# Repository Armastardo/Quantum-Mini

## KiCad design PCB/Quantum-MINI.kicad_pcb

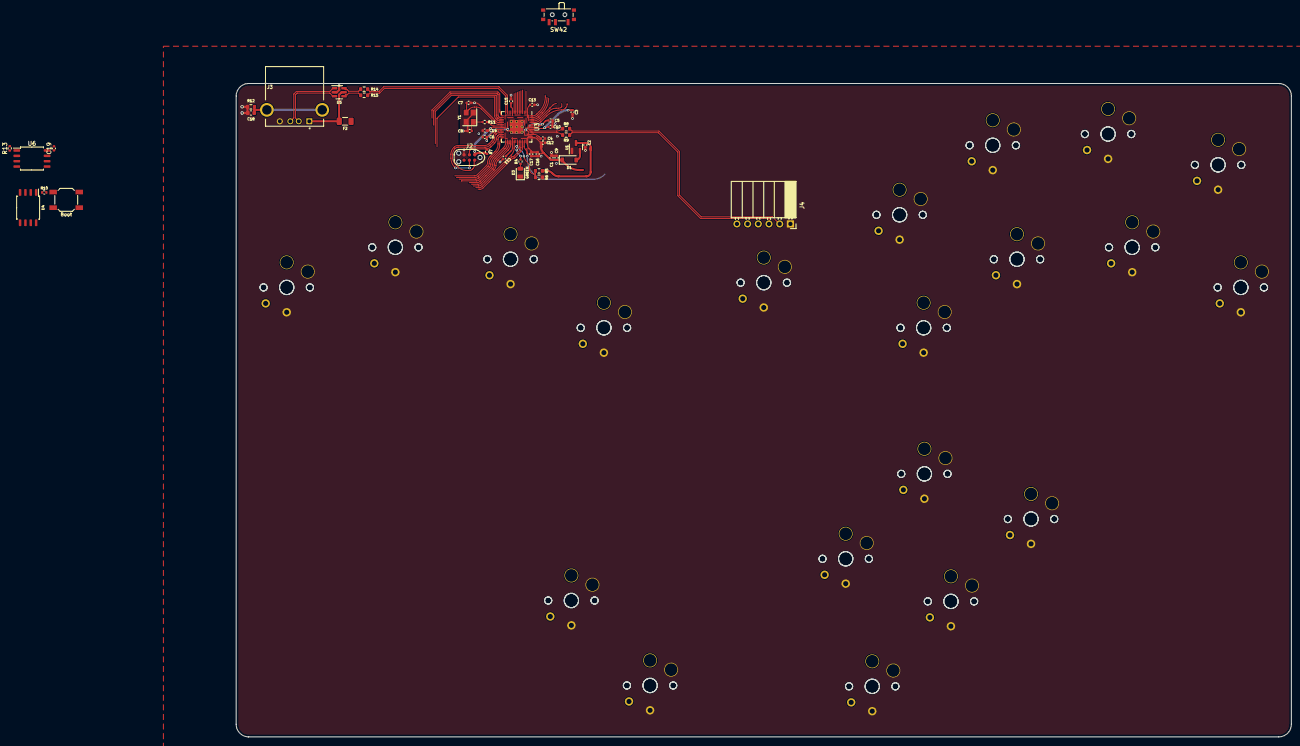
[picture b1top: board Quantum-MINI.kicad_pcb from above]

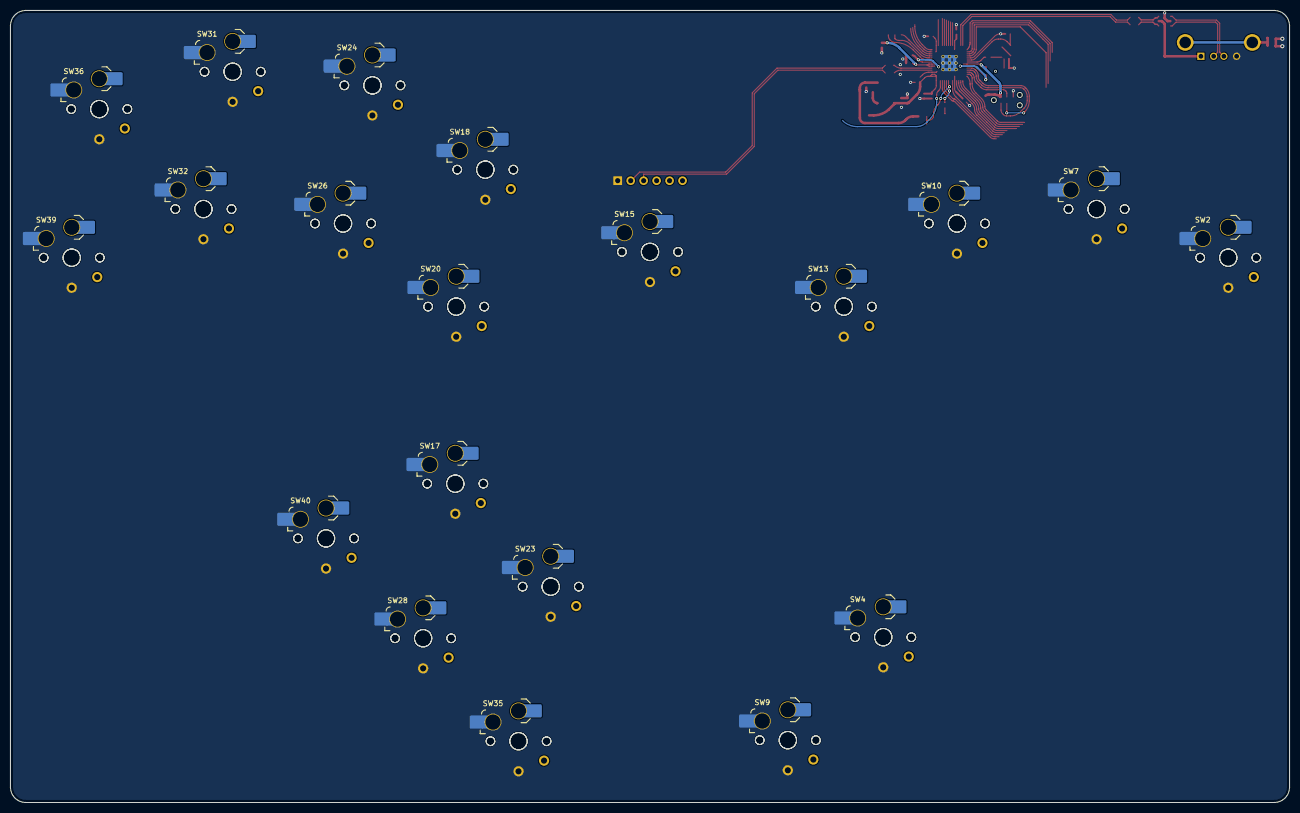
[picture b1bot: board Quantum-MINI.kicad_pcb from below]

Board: 2 copper layers, 250.6 x 155.2 mm, 85 parts (20 on the bottom side), 55 nets.

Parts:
C1, C2, C4, C10: 1uF; C_0402_1005Metric
C3, C5, C6, C11, C12, C13, C14, C15, C16, C17, C19: 100nF; C_0402_1005Metric
C7, C8: 22pF; C_0402_1005Metric
C9: 10uF; C_0402_1005Metric
C18: 4.7uf; C_0603_1608Metric
D1: Schottky Diode; D_SOD-123
D3: GREEN; LED_0805_2012Metric
F2: 500 mA; Fuse_1206_3216Metric
J2: JTAG_TC2030; CON_TC2030_outlined
J3: USB_A; GCT_USB1130-15-A_REVA
J4: Conn_01x06; PinSocket_1x06_P2.54mm_Horizontal
R4, R7, R10, R13: 10k; R_0402_1005Metric
R5: 5.6k; R_0603_1608Metric
R6: 10k; R_0603_1608Metric
R8, R9: 27; R_0603_1608Metric
R11: 1k; R_0402_1005Metric
R12: 1M; R_0603_1608Metric
R14, R15: 22; R_0603_1608Metric
SW1: Boot; SW_SPST_SKQG_WithStem
SW2, SW4, SW7, SW9, SW10, SW13, SW15, SW17, SW18, SW20, SW23, SW24, SW26, SW28, SW31, SW32, SW35, SW36, SW39, SW40: MX_SW_HS; SW_choc_v1_HS_1u
SW3, SW5, SW6, SW8, SW11, SW12, SW14, SW16, SW19, SW21, SW22, SW25, SW27, SW29, SW30, SW33, SW34, SW37, SW38, SW41: MX_SW_solder; SW_choc_v1_1u
SW42: SW_SPDT; SW_SPDT_PCM12
U1: XC6206; SOT-23
U3: RP2040; RP2040-QFN-56
U4, U6: W25Q128JVS; SOIC-8_5.23x5.23mm_P1.27mm
U5: USBLC6-2SC6; SOT-23-6
Y1: 12MHz; Crystal_SMD_3225-4Pin_3.2x2.5mm

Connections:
+1V1: C4.1, C5.1, C6.1, U3.23 (DVDD), U3.45 (VREG_VOUT), U3.50 (DVDD)
+3V3: C1.2, C3.1, C9.1, C10.1, C11.1, C12.1, C13.1, C14.1, C15.1, C16.1, C17.1, C19.1, D1.1 (K), J2.1 (VCC), R7.1, R10.2, R13.2, U3.1 (IOVDD), U3.10 (IOVDD), U3.22 (IOVDD), U3.33 (IOVDD), U3.42 (IOVDD), U3.43 (ADC_AVDD), U3.44 (VREG_VIN), U3.48 (USB_VDD), U3.49 (IOVDD), U4.8 (VCC), U6.8 (VCC)
+5V: C2.2, F2.2, J4.4, R5.1, U1.3 (VI)
/D_+: R8.2, U3.47 (D+)
/D_-: R9.2, U3.46 (D-)
/XTAL_O: C8.2, R11.1, Y1.1
A: SW28.2, SW29.1, U3.17 (GPIO14)
B: SW20.2, SW21.1, U3.38 (GPIO26/ADC0)
CS: SW1.2, SW42.2 (B), U3.56 (QSPI_SS_N)
C_DN: SW34.1, SW35.2, U3.18 (GPIO15)
C_LT: SW22.1, SW23.2, U3.16 (GPIO13)
C_RT: SW40.2, SW41.1, U3.27 (GPIO16)
C_UP: SW16.1, SW17.2, U3.15 (GPIO12)
D+: J4.2, R8.1
D-: J4.3, R9.1
DATA: J4.6, U3.40 (GPIO28/ADC2)
DOWN: SW10.2, SW11.1, U3.5 (GPIO3)
GND: C1.1, C2.1, C3.2, C4.2, C5.2, C6.2, C7.1, C8.1, C9.2, C10.2, C11.2, C12.2, C13.2, C14.2, C15.2, C16.2, C17.2, C18.2, C19.2, D3.1 (K), J2.5 (GND), J3.4 (GND), J4.1, R6.2, R12.1, SW1.1, SW2.1, SW3.2, SW4.1, SW5.2, SW6.2, SW7.1, SW8.2, SW9.1, SW10.1, SW11.2, SW12.2, SW13.1, SW14.2, SW15.1, SW16.2, SW17.1, SW18.1, SW19.2, SW20.1, SW21.2, SW22.2, SW23.1, SW24.1, SW25.2, SW26.1, SW27.2, SW28.1, SW29.2, SW30.2, SW31.1, SW32.1, SW33.2, SW34.2, SW35.1, SW36.1, SW37.2, SW38.2, SW39.1, SW40.1, SW41.2, U1.1 (GND), U3.19 (TESTEN), U3.57 (GND), U4.4 (GND), U5.2 (GND), U6.4 (GND), Y1.2, Y1.4
L: SW2.2, SW3.1, U3.7 (GPIO5)
LEFT: SW6.1, SW7.2, U3.6 (GPIO4)
LS: SW36.2, SW37.1, U3.31 (GPIO20)
M1: SW4.2, SW5.1, U3.8 (GPIO6)
M2: SW8.1, SW9.2, U3.9 (GPIO7)
MB1: R10.1, SW42.3 (C), U4.1 (~CS)
MB2: R13.1, SW42.1 (A), U6.1 (~CS)
MS: SW30.1, SW31.2, U3.29 (GPIO18)
unnamed: D1.2 (A), U1.2 (VO)
unnamed: D3.2 (A), R4.2
unnamed: C18.1, J3.5 (Shield), R12.2
unnamed: R14.1, U5.6 (I/O1)
unnamed: R15.2, U5.4 (I/O2)
PICO_LED: R4.1, U3.37 (GPIO25)
QSPI_CLK: U3.52 (QSPI_SCLK), U4.6 (CLK), U6.6 (CLK)
R: SW18.2, SW19.1, U3.39 (GPIO27/ADC1)
RIGHT: SW12.1, SW13.2, U3.4 (GPIO2)
SD0: U3.53 (QSPI_SD0), U4.5 (DI(IO0)), U6.5 (DI(IO0))
SD1: U3.55 (QSPI_SD1), U4.2 (DO(IO1)), U6.2 (DO(IO1))
SD2: U3.54 (QSPI_SD2), U4.3 (IO2), U6.3 (IO2)
SD3: U3.51 (QSPI_SD3), U4.7 (IO3), U6.7 (IO3)
START: SW14.1, SW15.2, U3.2 (GPIO0)
SWCLK: J2.4 (SWCLK), U3.24 (SWCLK)
SWD: J2.2 (SWDIO), U3.25 (SWDIO)
UP: SW38.1, SW39.2, U3.28 (GPIO17)
USBD+: R14.2, U3.13 (GPIO10)
USBD-: R15.1, U3.14 (GPIO11)
USBDBUS+: J3.3 (D+), U5.1 (I/O1)
USBDBUS-: J3.2 (D-), U5.3 (I/O2)
USBVBUS: F2.1, J3.1 (VBUS), U5.5 (VBUS)
VBUS_SENSE: R5.2, R6.1, U3.36 (GPIO24)
X: SW26.2, SW27.1, U3.32 (GPIO21)
XTAL_IN: C7.2, U3.20 (XTAL_IN), Y1.3
XTAL_OUT: R11.2, U3.21 (XTAL_OUT)
Y: SW24.2, SW25.1, U3.34 (GPIO22)
Z: SW32.2, SW33.1, U3.30 (GPIO19)
~RESET: J2.3 (~RST), R7.2, U3.26 (~RUN)

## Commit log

2023-08-23 Initial component placement
2023-08-30 Decided to use a daughterboard
    - Removed USB port
    - Re-arranged rp2040 circuit
    - Added USB passthrough
    - Adjusted board outline
